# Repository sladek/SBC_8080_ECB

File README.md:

## SBC 8080 ECB microcomputer

This is my attempt to build a single-board microcomputer based on the Intel 8080 CPU. It contains the following features:

- Extended 512k x 8-bit SRAM that can be fully accessed via paging.

- 128 x 8-bit FLASH EPROM that is accessible after RESET so it can contain a bootloader, which can be moved to SRAM and boot the operating system or monitor program.

- Programmable Interrupt Controller Intel 8259.

- Programmable Interval Timer Intel 8253, which is used for baud rate generation and can also generate an interrupt and be connected to the speaker.

- Universal Synchronous/Asynchronous Receiver/Transmitter (USART) Intel 8251 used as serial console so SBC can be accessed directly via RS232 interface.

- ECB bus interface, which can be used for microcomputer extensions. The ECB bus interface facilitates communication between the main processor and various peripheral devices, enabling system expansion and enhancing functionality. Additionally, it allows for the integration of specialized hardware components, which can further optimize performance and adaptability in various applications. History of ECB bus is described below.

- Voltage power supply for CPU: +5V, -5V, +12V which follows the requirement that -5V must be the first voltage present. It also contains inverter for -5V generation and a boost converter from 5V to 12V so the SBC can be powered only from one +5V power supply.

Here you can find a schematics for the SBC. Kicad files are also available in this repository. 
[SBC_8080_ECB schematics.](Documentation/SBC_8080_ECB_.pdf)

## ECB bus history

(https://www.retrobrewcomputers.org/doku.php?id=boards:ecb:start)

Below is an image depicting the latest definition of the ECB bus as utilized by the RetroBrew Computers group. It also addresses issues related to the /RESET and /RESOUT pin definitions and the solutions implemented. This design incorporates a 3-pin jumper header to allow for the selection of the appropriate configuration.

The German firm Kontron defined what is believed to be the earliest bus using the 96-pin DIN 41612 EuroCard connectors. The bus for their Z80 offering used only the A-row and C-row pins; the B-row was left entirely unused to allow for the use of 64-pin connectors in the 96-pin format.

The earliest known RetroBrew bus definition included B-row pin definitions to facilitate the anticipated expansion of the Z80 bus to other processors, particularly Intel. To this day, the ECB SBC v2 (Z80) does not use the B-row pins.

One error occurred in defining the first RetroBrew bus: confusion between signals RESET (C-31) and RESOUT (C-26). The error resulted in a bad guess at what Kontron's intentions were with these two signals. SBC v1 (Z80) used RESET as an output from the CPU board to peripheral boards and did not use the RESOUT signal at all. Peripheral boards were designed with this assumption. When it was pointed out several years ago (I am unsure of the date) that Kontron's intention was for RESET to be an input to the CPU board only and that the CPU board would then put out a signal, RESOUT, to all of the peripheral boards in the system.

The resolution to the above mistake is that all the newer CPU and peripheral boards have a reset selection jumper to select which RetroBrew reset convention is to be used. Look for a 3-pin jumper header: shorting pins 1-2 indicates the older, erroneous, reset convention for use with older boards; shorting pins 2-3 indicates the use of the Kontron convention. The Kontron convention is essential if RESET is to be received from any of the ECB backplanes, and only newer boards are allowed in such a system. Old CPU boards have a 2-pin Reset (in) connection as well as a reset switch right on the CPU card.

## Generate baud rate for 8251

### Response:

The **8253 Programmable Interval Timer (PIT)** can be used as a **baud rate generator** for serial communication by generating clock pulses at the required frequency. This is done by programming one of its three counters to divide an input clock signal down to the desired baud rate.

### Steps to Use 8253 as Baud Rate Generator

1. **Select the Counter:** 
   The 8253 has three counters (Counter 0, Counter 1, Counter 2). You need to choose one for generating the baud rate.

2. **Provide the Clock Input:**
   
   The 8253 typically receives a clock input (e.g., **1.8432 MHz or some
   other standard clock frequency**). Ensure the clock is stable and properly connected.

3. **Calculate the Divider Value:**  
   The baud rate is generated by dividing the input clock using a counter. The formula is:
   
    Input Frequency RateDivider=Baud RateClock Input Frequency​
   
   For example, if the input clock is **1.8432 MHz** and you need a baud rate of **9600**,
   the divider value is:
   
   1843200÷9600=192

4. **Program the 8253:**
   
   - Load the
     appropriate **mode** (typically Mode 2 – Rate Generator or Mode 3 – Square Wave).
   
   - Load the **divider value** into the selected counter.
   
   - Start the timer and route its output to the serial communication hardware (like 8251 USART or UART).

5. **Connect Output to Serial**
   Device: The output of the **8253 counter** is connected to the baud rate clock input of a serial communication device like the **8251 USART** or a UART module.

### Example: Setting Baud rate for 9600 using 1.8432 MHz Clock

- Use **Counter 0** of **8253**.

- Program it in **Mode 2 (Rate Generator)**.

- Load **192** as the divider value.

#### **Programming Steps (for an x86-based system)**

Assembly code

```
    MOV AL, 34H    ; Control Word: Counter 0, Mode 2, LSB/MSB
    OUT 43H, AL    ; Send control word to 8253
    MOV AL, 192    ; Load LSB (Least Significant Byte)
    OUT 40H, AL    ; Send LSB to Counter 0
    MOV AL, 0      ; Load MSB (Most Significant Byte)
    OUT 40H, AL    ; Send MSB to Counter 0
```

- **43H** → Control port of **8253**

- **40H** → Counter 0 data port

### **Modes Used in 8253 for Baud Rate**

- **Mode 2 (Rate Generator)** → Outputs a
   frequency suitable for baud generation.

- **Mode 3 (Square Wave Generator)** → Outputs a symmetrical square wave (useful in some applications).

### **Final Connection**

The **OUT0** pin of **8253** (if using Counter 0) is connected to the **clock input** of **8251 USART or UART** for serial communication.

### **Summary**

- Use **Mode 2 (Rate Generator)**

- Compute the **divider value** using the formula

- Program the **control word and counter value**

- Connect **output** to the **serial device** clock input.

This setup allows the **8253** to act as a **baud rate generator** for serial communication.

## Baud rate divider

As crystal frequency is 18.432 Mhz and it is outputted from I8224, we can use that frequency to generate baud rate clock signal for I8251. Below is the solution.

74LS390 contains two decade counters, where /CP0 → Q0 functions as a divider by 2, and /CP1 → Q1, Q2, Q3 operates as a divider by 5. We send an 18.432 MHz clock signal from I8224 to /CP1; it is divided by 5 and then fed to /CP0, where it is divided by 2. This arrangement will generate a square signal with an exact 50% duty cycle. The output signal from Q0 is then fed to the I8252 timer, where the appropriate baud rate can be generated.

### Shadow FLASH select logic

In the picture below you can see shadow FLASH select logic schematics.

After /RESET (at this point, the /SRAMSELECT signal from the IO decoder is HIGH), /SRAM_SEL is HIGH and /FLASH_SEL is LOW. Now /SRAM_OE is HIGH (the DATA from RAM are in high impedance, although writing is not prohibited), so the /RD signal has no effect on /SRAM_OE. Only changes in /MEMRQ will impact the /FLASH_MREQ signal, which means that only FLASH memory can be accessed, either for reading or for writing. So it is also possible to flash the memory using a programmer connected to the ECB bus. A simulation has also been conducted in Verilog (via iVerilog) and can be seen below.

```
/*
 Test bench
*/

`timescale 10ns/10ns

module shadow_flash_select_logic_tb();

   reg MEMRQ, RESET, SRAMSEL, RD;
   wire SRAM_SEL, FLASH_SEL, SRAM_OE, FLASH_MEMRQ;

   initial begin
      $dumpfile ("shadow_flash_select_logic.vcd");
      $dumpvars;
   end

  initial begin
     RESET = 1;
     #10
     RESET = 0;
     #5
     RESET = 1;
  end

  initial begin
     SRAMSEL = 1;
     RD = 1;
     MEMRQ = 1;
  end

  initial begin
     #50;
       RD = 0;
     #50;
       RD = 1;
     #50;
       MEMRQ = 0;
     #50;
       MEMRQ = 1;
     #50
       SRAMSEL = 0;
     #50
       RD = 0;
     #50
       RD = 1;
     #50
       MEMRQ = 0;
     #50
       MEMRQ = 1;
 end

  initial begin
    #500;
    $finish;
  end

   // The Netlist
   nand(SRAM_SEL, RESET, FLASH_SEL);
   nand(FLASH_SEL, SRAMSEL, SRAM_SEL);
   or(SRAM_OE, SRAM_SEL, RD);
   or(FLASH_MREQ, FLASH_SEL, MEMRQ); 

endmodule
```

Simulation result in gtkwave is shown below.

### ECB bus data direction

As we also have to send and read data from the ECB bus, we have to make sure that bus data buffers are properly directed if there is a bus request (BUSRQ) from the bus itself.

Signal DATA_DIR Select the direction of the data buffer. If DATA_DIR is log 0, data direction is from the board to the ECB bus, and if DATA_DIR is log 1, 1data can flow from the ECB bus to the board.

This is done by the circuit below. Basically, the upper part (/MEMRQ, /RD, /IOSEL, which is low when internal peripherals are selected) takes care of standard operations, and the upper part is involved when there is a request from the ECB bus. (/RD, /BUSAK)

Below you can see simulation code and simulation result.

```
/*
 Test bench
*/

`timescale 10ns/10ns

module shadow_flash_select_logic_tb();

   reg MREQ, IOSEL, RD, BUSAK;
   wire DATA_DIR, MREQ_IOSEL, RD_BUSAK, DATAEN;

   initial begin
      $dumpfile ("ecb_data_dir_logic.vcd");
      $dumpvars;
   end

  initial begin
    MREQ = 1;
    IOSEL = 1;
    RD = 1;
    BUSAK = 1;
/* MREQ and RD */
    #50
      MREQ = 0;
    #10
      RD = 0;
    #50
      RD = 1;
    #10
      MREQ = 1;
/* IOSEL and RD */
    #50
      IOSEL = 0;
    #10
      RD = 0;
    #50
      RD = 1;
    #10
      IOSEL = 1;
/* BUSAK and RD */
    #50
      BUSAK = 0;
    #50
      BUSAK = 1;
    #50
      RD = 0;
    #50
      RD = 1;
  end

  initial begin
    #500;
    $finish;
  end

   // The Netlist
   and(MREQ_IOSEL, MREQ, IOSEL);
   nand(RD_BUSAK, RD, BUSAK);
   or(RD_MREQ_IOSEL, MREQ_IOSEL, RD);
   and(DATA_DIR, RD_MREQ_IOSEL, RD_BUSAK);

endmodule
```

And the simulation result is below.

### Peripherals address space

Internal peripherals are selected by the following decoder.

The address space with this circuit is 0x40 – 0x7f.

Where base addresses of peripherals are in the following table.

|                                                   |               |
| ------------------------------------------------- | ------------- |
| Peripheral                                        | Address range |
| PIC 8259A                                         | 0x40 – 047    |
| PIT 8253                                          | 0x48 - 0x4F   |
| SIO 8251                                          | 0x50 - 0x57   |
| RAM bank/ SD card select register (/BANK/SD_SEL ) | 0x58 - 0x5F   |
| RAM select signal (/SRAMSEL)                      | 0x78 - 0x7F   |

Below is verilog simulation result for the decoder.

And the source code. I intentionally use primitives for simulation of 74LS138 to prevent some simulation glitches I got when I tried to use behavioral modeling. It is quite simplified as I’ve just wanted to verify address space for peripherals.

```
/*
 Test bench
*/

`timescale 10ns/10ns

module SN74LS138(input [2:0] ADDR, input E0_n, E1_n, E2, output wire [7:0] Y_n);

  not(E2_n, E2);
  nor(ENBL, E2_n, E0_n, E1_n);
  not(A_n, ADDR[0]);
  not(B_n, ADDR[1]);
  not(C_n, ADDR[2]);
  not(A, A_n);
  not(B, B_n);
  not(C, C_n);
  nand(Y_n[0], A_n, B_n, C_n, ENBL);
  nand(Y_n[1], A, B_n, C_n, ENBL);
  nand(Y_n[2], A_n, B, C_n, ENBL);
  nand(Y_n[3], A, B, C_n, ENBL);
  nand(Y_n[4], A_n, B_n, C, ENBL);
  nand(Y_n[5], A, B_n, C, ENBL);
  nand(Y_n[6], A_n, B, C, ENBL);
  nand(Y_n[7], A, B, C, ENBL);

endmodule

module peripheral_decoder_tb();
  reg  [7:0] ADDRESS = 0;
  reg  A6, A7, IORQ_n;
  wire [7:0] OUT;
  wire A7_n, A7_A6, IOSEL_n, PIC_SEL_n, PIT_SEL_n, SIO_SEL_n, SD_SEL_n, BANK_SD_SEL_n;
  integer I = 0;

   initial begin
      $dumpfile ("peripheral_decoder.vcd");
      $dumpvars;
   end

  initial begin
    IORQ_n = 0;
    ADDRESS = 'h00;
    for ( I = 'h3F ; I < 'hff; I = I + 1) begin
      #5 ADDRESS = I;
    end

  end

  initial begin
    #350;
    $finish;
  end
  assign PIC_SEL_n = OUT[0];
  assign PIT_SEL_n = OUT[1];
  assign SIO_SEL_n = OUT[2];
  assign SD_SEL_n = OUT[3];
  assign BANK_SD_SEL_n = OUT[7];
  // The Netlist
  SN74LS138 ls138(ADDRESS[5:3], IOSEL_n, IOSEL_n, 1'b1 , OUT);
  not(A7_n, ADDRESS[7]);
  nand(A7_A6, A7_n, ADDRESS[6]);
  or(IOSEL_n, A7_A6, IORQ_n);
endmodule
```

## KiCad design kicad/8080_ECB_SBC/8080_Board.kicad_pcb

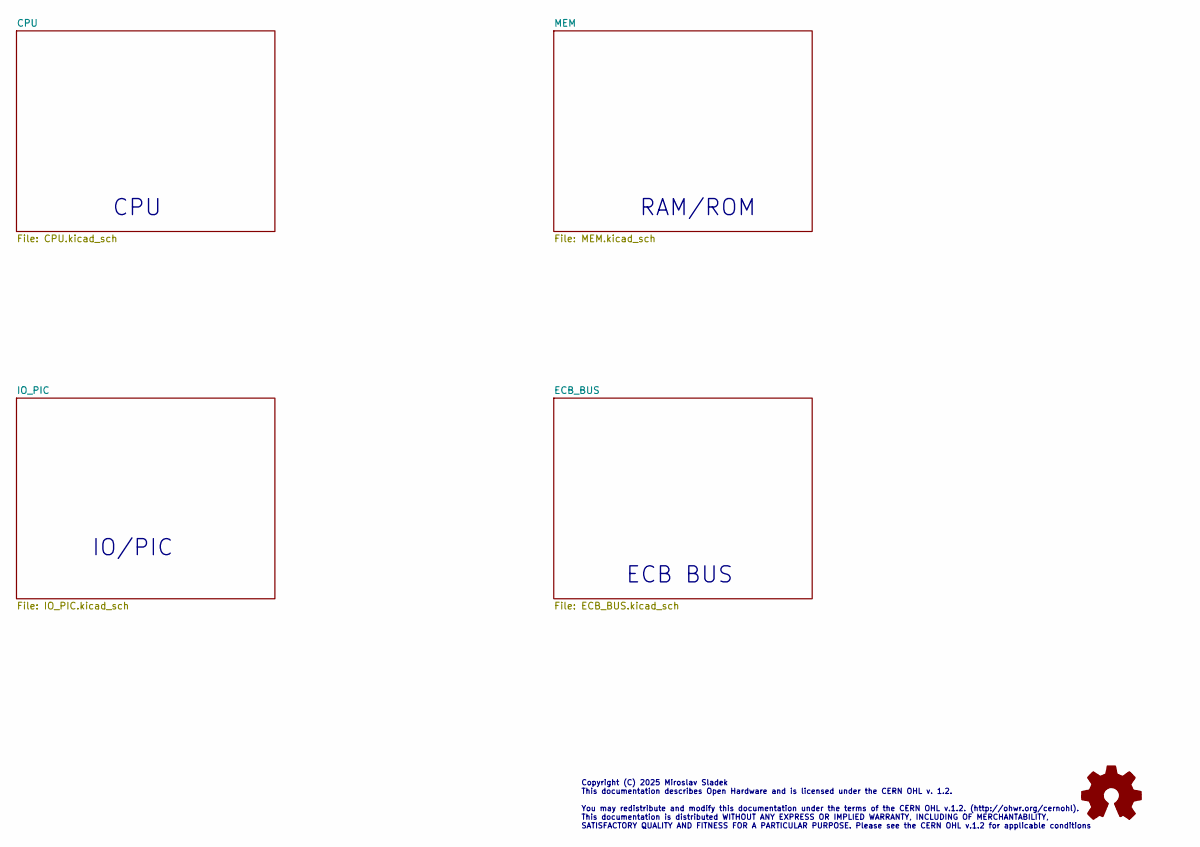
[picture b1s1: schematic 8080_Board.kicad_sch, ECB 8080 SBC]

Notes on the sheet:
RAM/ROM
IO/PIC
CPU
ECB BUS
Copyright (C) 2025 Miroslav Sladek This documentation describes Open Hardware and is licensed under the CERN OHL v. 1.2. You may redistribute and modify this documentation under the terms of the CERN OHL v.1.2. (http://ohwr.org/cernohl). This documentation is distributed WITHOUT ANY EXPRESS OR IMPL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

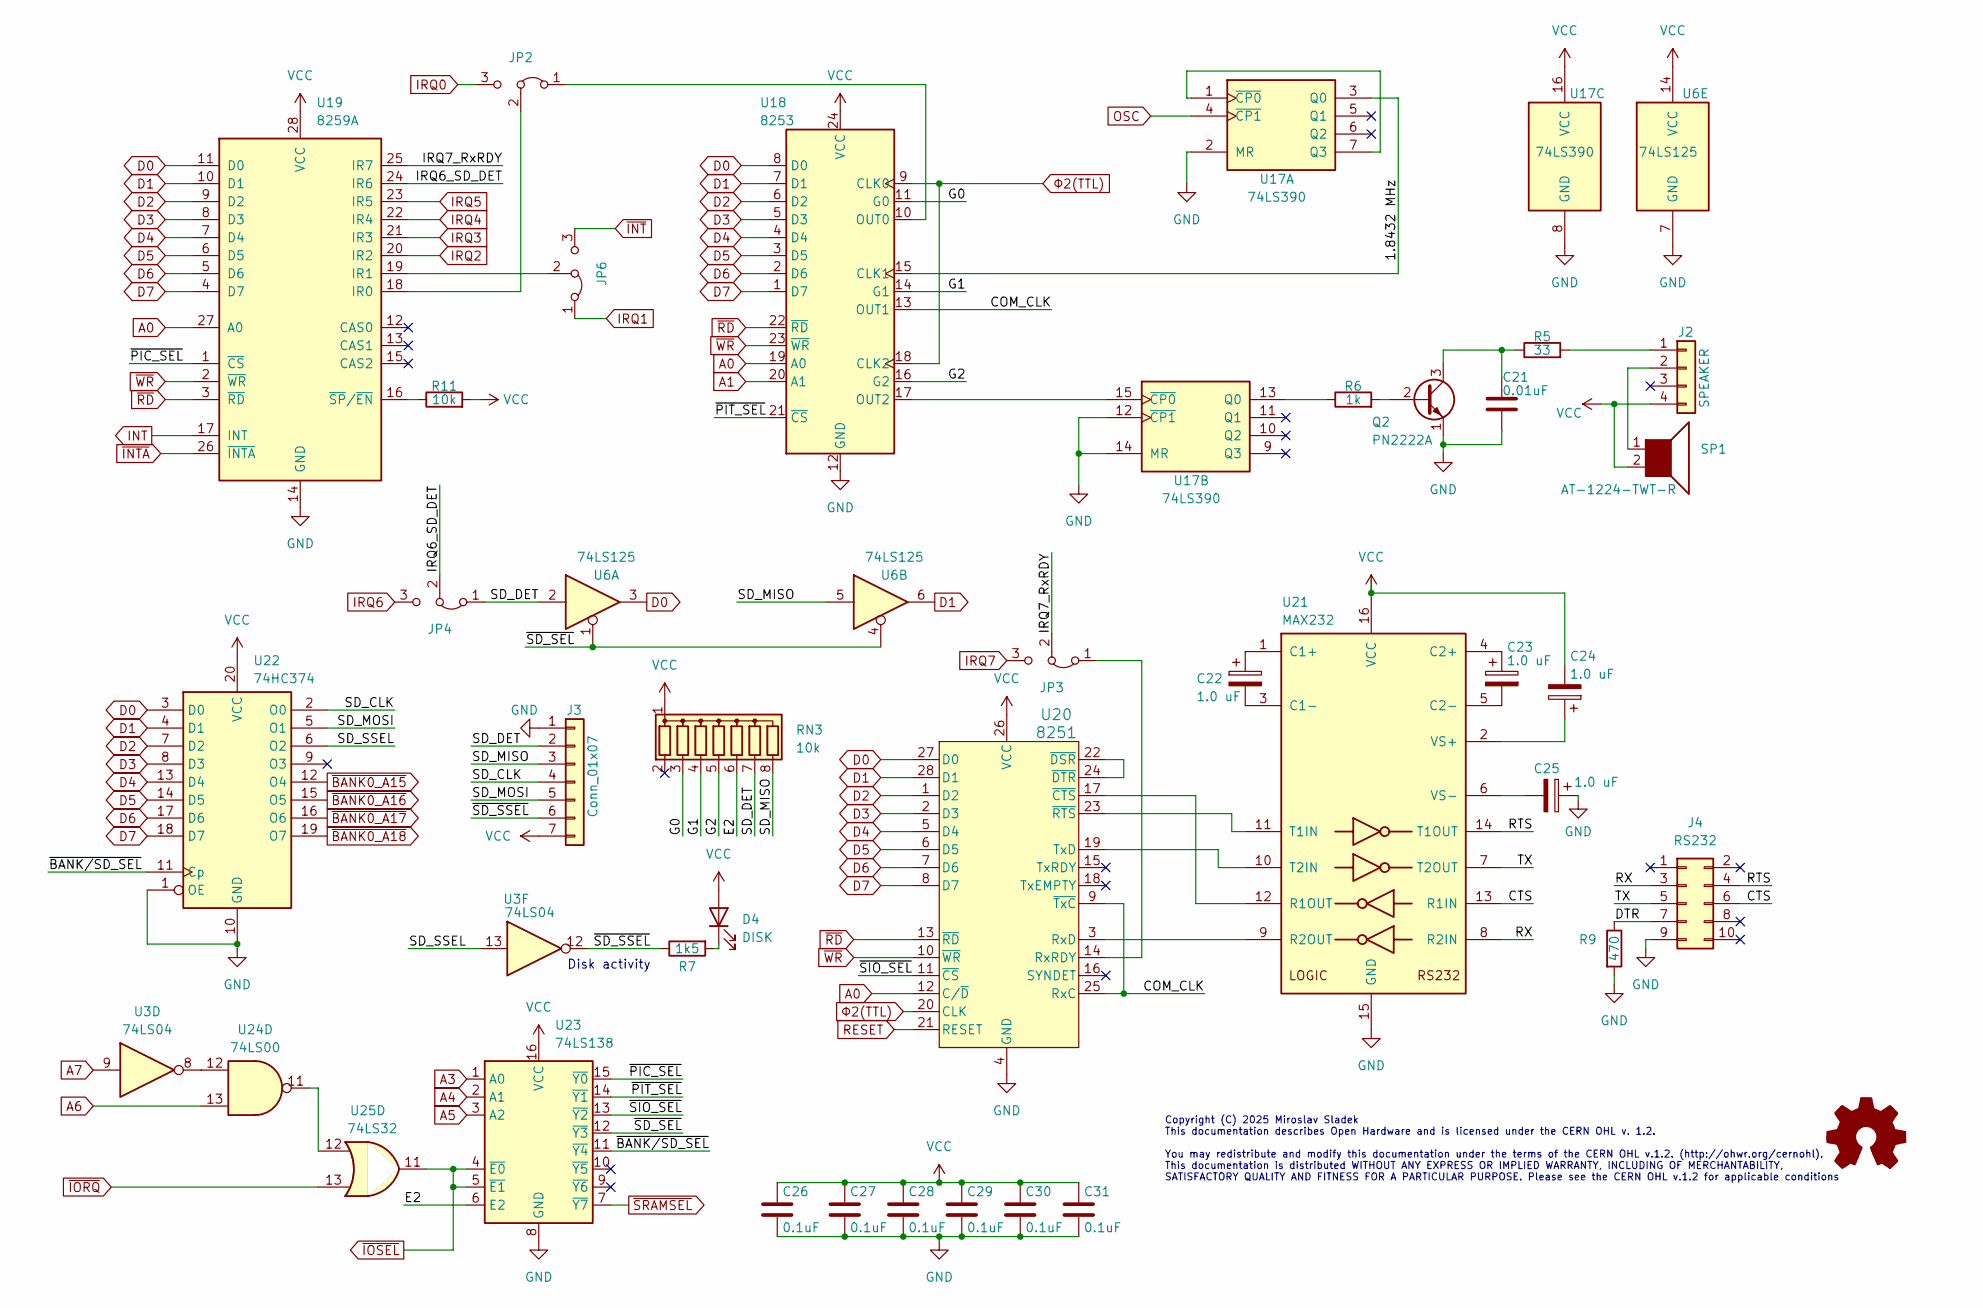
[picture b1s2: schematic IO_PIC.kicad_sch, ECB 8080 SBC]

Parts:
C21: 0.01uF; C_Disc_D3.0mm_W1.6mm_P2.50mm
C22, C23, C24, C25: 1.0 uF; C_Rect_L7.2mm_W3.0mm_P5.00mm_FKS2_FKP2_MKS2_MKP2
C26, C27, C28, C29, C30, C31: 0.1uF; C_Disc_D4.3mm_W1.9mm_P5.00mm
D4: DISK; LED_D3.0mm
J2: SPEAKER; PinHeader_1x04_P2.54mm_Vertical
J3: Conn_01x07; PinSocket_1x07_P2.54mm_Vertical
J4: RS232; PinHeader_2x05_P2.54mm_Vertical
JP2, JP3, JP4, JP6: Jumper_3_Bridged12; PinHeader_1x03_P2.54mm_Vertical
Q2: PN2222A; TO-92_Inline
R5: 33; R_Axial_DIN0204_L3.6mm_D1.6mm_P7.62mm_Horizontal
R6: 1k; R_Axial_DIN0204_L3.6mm_D1.6mm_P7.62mm_Horizontal
R7: 1k5; R_Axial_DIN0204_L3.6mm_D1.6mm_P7.62mm_Horizontal
R9: 470; R_Axial_DIN0204_L3.6mm_D1.6mm_P7.62mm_Horizontal
R11: 10k; R_Axial_DIN0204_L3.6mm_D1.6mm_P7.62mm_Horizontal
RN3: 10k; R_Array_SIP8
SP1: AT-1224-TWT-R; MagneticBuzzer_ProSignal_ABT-410-RC
U3: 74LS04; DIP-14_W7.62mm_Socket
U6: 74LS125; DIP-14_W7.62mm_Socket
U17: 74LS390; DIP-16_W7.62mm_Socket
U18: 8253; DIP-24_W15.24mm_Socket
U19: 8259A; DIP-28_W15.24mm_Socket
U20: 8251; DIP-28_W15.24mm_Socket
U21: MAX232; DIP-16_W7.62mm_Socket
U22: 74HC374; DIP-20_W7.62mm_Socket
U23: 74LS138; DIP-16_W7.62mm_Socket
U24: 74LS00; DIP-14_W7.62mm_Socket
U25: 74LS32; DIP-14_W7.62mm_Socket

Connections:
/IO_PIC/1.8432 MHz: U17.3 (Q0), U18.15 (CLK1)
/IO_PIC/COM_CLK: U18.13 (OUT1), U20.9 (~TxC), U20.25 (RxC)
/IO_PIC/CTS: J4.6, U21.13 (R1IN)
/IO_PIC/DTR: J4.7, R9.1
/IO_PIC/E2: RN3.6 (R5), U23.6 (E2)
/IO_PIC/G0: RN3.3 (R2), U18.11 (G0)
/IO_PIC/G1: RN3.4 (R3), U18.14 (G1)
/IO_PIC/G2: RN3.5 (R4), U18.16 (G2)
/IO_PIC/IRQ6_SD_DET: JP4.2 (C), U19.24 (IR6)
/IO_PIC/IRQ7_RxRDY: JP3.2 (C), U19.25 (IR7)
/IO_PIC/RTS: J4.4, U21.14 (T1OUT)
/IO_PIC/RX: J4.3, U21.8 (R2IN)
/IO_PIC/SD_CLK: J3.4, U22.2 (O0)
/IO_PIC/SD_DET: J3.2, JP4.1 (A), RN3.7 (R6), U6.2
/IO_PIC/SD_MISO: J3.3, RN3.8 (R7), U6.5
/IO_PIC/SD_MOSI: J3.5, U22.5 (O1)
/IO_PIC/SD_SSEL: U3.13, U22.6 (O2)
/IO_PIC/TX: J4.5, U21.7 (T2OUT)
/IO_PIC/~BANK/SD_SEL: U22.11 (Cp), U23.11 (~Y4)
/IO_PIC/~PIC_SEL: U19.1 (~CS), U23.15 (~Y0)
/IO_PIC/~PIT_SEL: U18.21 (~CS), U23.14 (~Y1)
/IO_PIC/~SD_SEL: U6.1, U6.4, U23.12 (~Y3)
/IO_PIC/~SD_SSEL: J3.6, R7.1, U3.12
/IO_PIC/~SIO_SEL: U20.11 (~CS), U23.13 (~Y2)
A0: U18.19 (A0), U19.27 (A0), U20.12 (C/~D); also elsewhere on the board
A1: U18.20 (A1); also elsewhere on the board
A3: U23.1 (A0); also elsewhere on the board
A4: U23.2 (A1); also elsewhere on the board
A5: U23.3 (A2); also elsewhere on the board
A6: U24.13; also elsewhere on the board
A7: U3.9; also elsewhere on the board
D0: U6.3, U18.8 (D0), U19.11 (D0), U20.27 (D0), U22.3 (D0); also elsewhere on the board
D1: U6.6, U18.7 (D1), U19.10 (D1), U20.28 (D1), U22.4 (D1); also elsewhere on the board
D2: U18.6 (D2), U19.9 (D2), U20.1 (D2), U22.7 (D2); also elsewhere on the board
D3: U18.5 (D3), U19.8 (D3), U20.2 (D3), U22.8 (D3); also elsewhere on the board
D4: U18.4 (D4), U19.7 (D4), U20.5 (D4), U22.13 (D4); also elsewhere on the board
D5: U18.3 (D5), U19.6 (D5), U20.6 (D5), U22.14 (D5); also elsewhere on the board
D6: U18.2 (D6), U19.5 (D6), U20.7 (D6), U22.17 (D6); also elsewhere on the board
D7: U18.1 (D7), U19.4 (D7), U20.8 (D7), U22.18 (D7); also elsewhere on the board
INT: U19.17 (INT); also elsewhere on the board
IRQ0: JP2.3 (B); also elsewhere on the board
IRQ1: JP6.1 (A); also elsewhere on the board
IRQ2: U19.20 (IR2); also elsewhere on the board
IRQ3: U19.21 (IR3); also elsewhere on the board
IRQ4: U19.22 (IR4); also elsewhere on the board
IRQ5: U19.23 (IR5); also elsewhere on the board
IRQ6: JP4.3 (B); also elsewhere on the board
IRQ7: JP3.3 (B); also elsewhere on the board
unnamed: D4.1 (K), R7.2
unnamed: J2.1, R5.2
unnamed: J2.2, SP1.1
unnamed: JP2.1 (A), U18.10 (OUT0)
unnamed: JP2.2 (C), U19.18 (IR0)
unnamed: JP3.1 (A), U20.14 (RxRDY)
unnamed: JP6.2 (C), U19.19 (IR1)
unnamed: Q2.2 (B), R6.2
unnamed: C21.1, Q2.3 (C), R5.1
unnamed: U17.1 (~CP0), U17.7 (Q3)
unnamed: R6.1, U17.13 (Q0)
unnamed: U17.15 (~CP0), U18.17 (OUT2)
unnamed: R11.1, U19.16 (~SP/~EN)
unnamed: U20.3 (RxD), U21.9 (R2OUT)
unnamed: U20.19 (TxD), U21.10 (T2IN)
unnamed: U20.17 (~CTS), U21.12 (R1OUT)
unnamed: U20.22 (~DSR), U20.24 (~DTR)
unnamed: U20.23 (~RTS), U21.11 (T1IN)
unnamed: C22.1, U21.1 (C1+)
unnamed: C22.2, U21.3 (C1-)
unnamed: C23.1, U21.4 (C2+)
unnamed: C23.2, U21.5 (C2-)
unnamed: C24.1, U21.2 (VS+)
unnamed: C25.2, U21.6 (VS-)
unnamed: U24.11, U25.12
unnamed: U3.8, U24.12
OSC: U17.4 (~CP1); also elsewhere on the board
RESET: U20.21 (RESET); also elsewhere on the board
VCC: C24.2, C26.1, C27.1, C28.1, C29.1, C30.1, C31.1, D4.2 (A), J2.4, J3.7, R11.2, RN3.1 (common), SP1.2, U6.14 (VCC), U17.16 (VCC), U18.24 (VCC), U19.28 (VCC), U20.26 (VCC), U21.16 (VCC), U22.20 (VCC), U23.16 (VCC); also elsewhere on the board
~BANK0_A15: U22.12 (O4); also elsewhere on the board
~BANK0_A16: U22.15 (O5); also elsewhere on the board
~BANK0_A17: U22.16 (O6); also elsewhere on the board
~BANK0_A18: U22.19 (O7); also elsewhere on the board
~INTA: U19.26 (~INTA); also elsewhere on the board
~INT: JP6.3 (B); also elsewhere on the board
~IORQ: U25.13; also elsewhere on the board
~IOSEL: U23.4 (~E0), U23.5 (~E1), U25.11; also elsewhere on the board
~RD: U18.22 (~RD), U19.3 (~RD), U20.13 (~RD); also elsewhere on the board
~SRAMSEL: U23.7 (~Y7); also elsewhere on the board
~WR: U18.23 (~WR), U19.2 (~WR), U20.10 (~WR); also elsewhere on the board
Φ2(TTL): U18.9 (CLK0), U18.18 (CLK2), U20.20 (CLK); also elsewhere on the board

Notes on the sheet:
Disk activity
Copyright (C) 2025 Miroslav Sladek This documentation describes Open Hardware and is licensed under the CERN OHL v. 1.2. You may redistribute and modify this documentation under the terms of the CERN OHL v.1.2. (http://ohwr.org/cernohl). This documentation is distributed WITHOUT ANY EXPRESS OR IMPL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

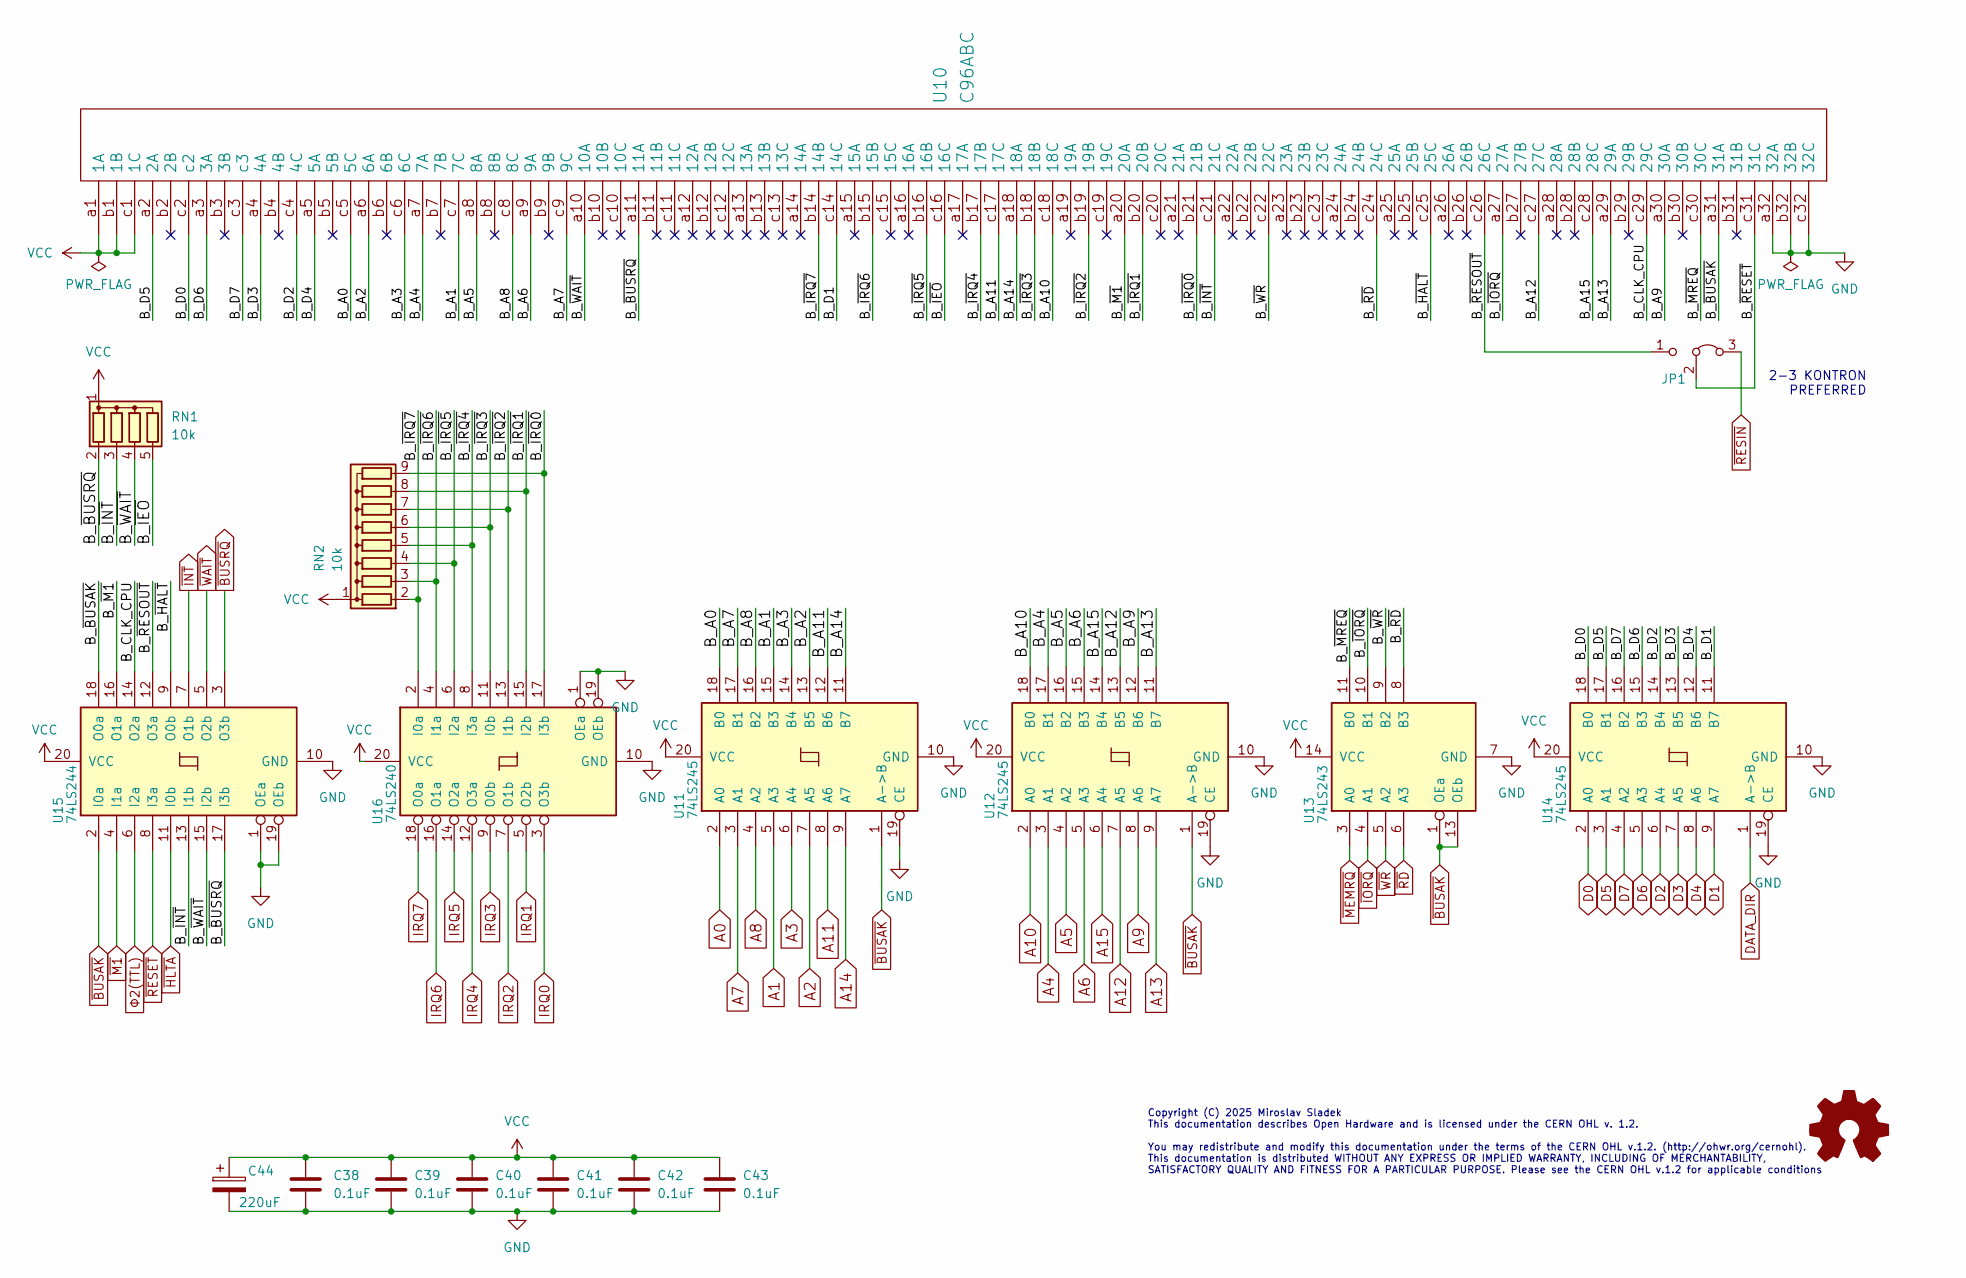
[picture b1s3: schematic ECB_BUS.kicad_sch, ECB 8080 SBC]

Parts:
C38, C39, C40, C41, C42, C43: 0.1uF; C_Disc_D4.3mm_W1.9mm_P5.00mm
C44: 220uF; CP_Radial_D5.0mm_P2.00mm
JP1: Jumper_3_Bridged23; PinHeader_1x03_P2.54mm_Vertical
RN1: 10k; R_Array_SIP5
RN2: 10k; R_Array_SIP9
U10: C96ABC; DIN41612_C_3x32_Male_Horizontal_THT
U11, U12, U14: 74LS245; DIP-20_W7.62mm_Socket
U13: 74LS243; DIP-14_W7.62mm_Socket
U15: 74LS244; DIP-20_W7.62mm_Socket
U16: 74LS240; DIP-20_W7.62mm_Socket

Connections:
/ECB_BUS/B_A0: U10.c5 (5C), U11.18 (B0)
/ECB_BUS/B_A1: U10.c7 (7C), U11.15 (B3)
/ECB_BUS/B_A2: U10.a6 (6A), U11.13 (B5)
/ECB_BUS/B_A3: U10.c6 (6C), U11.14 (B4)
/ECB_BUS/B_A4: U10.a7 (7A), U12.17 (B1)
/ECB_BUS/B_A5: U10.a8 (8A), U12.16 (B2)
/ECB_BUS/B_A6: U10.a9 (9A), U12.15 (B3)
/ECB_BUS/B_A7: U10.c9 (9C), U11.17 (B1)
/ECB_BUS/B_A8: U10.c8 (8C), U11.16 (B2)
/ECB_BUS/B_A9: U10.a30 (30A), U12.12 (B6)
/ECB_BUS/B_A10: U10.c18 (18C), U12.18 (B0)
/ECB_BUS/B_A11: U10.c17 (17C), U11.12 (B6)
/ECB_BUS/B_A12: U10.c27 (27C), U12.13 (B5)
/ECB_BUS/B_A13: U10.a29 (29A), U12.11 (B7)
/ECB_BUS/B_A14: U10.a18 (18A), U11.11 (B7)
/ECB_BUS/B_A15: U10.c28 (28C), U12.14 (B4)
/ECB_BUS/B_CLK_CPU: U10.c29 (29C), U15.14 (O2a)
/ECB_BUS/B_D0: U10.c2, U14.18 (B0)
/ECB_BUS/B_D1: U10.c14 (14C), U14.11 (B7)
/ECB_BUS/B_D2: U10.c4 (4C), U14.14 (B4)
/ECB_BUS/B_D3: U10.a4 (4A), U14.13 (B5)
/ECB_BUS/B_D4: U10.a5 (5A), U14.12 (B6)
/ECB_BUS/B_D5: U10.a2 (2A), U14.17 (B1)
/ECB_BUS/B_D6: U10.a3 (3A), U14.15 (B3)
/ECB_BUS/B_D7: U10.c3, U14.16 (B2)
/ECB_BUS/B_~BUSAK: U10.a31 (31A), U15.18 (O0a)
/ECB_BUS/B_~BUSRQ: RN1.2 (R1), U10.a11 (11A), U15.17 (I3b)
/ECB_BUS/B_~HALT: U10.c25 (25C), U15.9 (O0b)
/ECB_BUS/B_~IEO: RN1.5 (R4), U10.c16 (16C)
/ECB_BUS/B_~INT: RN1.3 (R2), U10.c21 (21C), U15.13 (I1b)
/ECB_BUS/B_~IORQ: U10.a27 (27A), U13.10 (B1)
/ECB_BUS/B_~IRQ0: RN2.9 (R8), U10.b21 (21B), U16.17 (I3b)
/ECB_BUS/B_~IRQ1: RN2.8 (R7), U10.b20 (20B), U16.15 (I2b)
/ECB_BUS/B_~IRQ2: RN2.7 (R6), U10.b19 (19B), U16.13 (I1b)
/ECB_BUS/B_~IRQ3: RN2.6 (R5), U10.b18 (18B), U16.11 (I0b)
/ECB_BUS/B_~IRQ4: RN2.5 (R4), U10.b17 (17B), U16.8 (I3a)
/ECB_BUS/B_~IRQ5: RN2.4 (R3), U10.b16 (16B), U16.6 (I2a)
/ECB_BUS/B_~IRQ6: RN2.3 (R2), U10.b15 (15B), U16.4 (I1a)
/ECB_BUS/B_~IRQ7: RN2.2 (R1), U10.b14 (14B), U16.2 (I0a)
/ECB_BUS/B_~M1: U10.a20 (20A), U15.16 (O1a)
/ECB_BUS/B_~MREQ: U10.c30 (30C), U13.11 (B0)
/ECB_BUS/B_~RD: U10.c24 (24C), U13.8 (B3)
/ECB_BUS/B_~RESET: JP1.2 (C), U10.c31 (31C)
/ECB_BUS/B_~RESOUT: JP1.1 (A), U10.c26 (26C), U15.12 (O3a)
/ECB_BUS/B_~WAIT: RN1.4 (R3), U10.a10 (10A), U15.15 (I2b)
/ECB_BUS/B_~WR: U10.c22 (22C), U13.9 (B2)
A0: U11.2 (A0); also elsewhere on the board
A1: U11.5 (A3); also elsewhere on the board
A2: U11.7 (A5); also elsewhere on the board
A3: U11.6 (A4); also elsewhere on the board
A4: U12.3 (A1); also elsewhere on the board
A5: U12.4 (A2); also elsewhere on the board
A6: U12.5 (A3); also elsewhere on the board
A7: U11.3 (A1); also elsewhere on the board
A8: U11.4 (A2); also elsewhere on the board
A9: U12.8 (A6); also elsewhere on the board
A10: U12.2 (A0); also elsewhere on the board
A11: U11.8 (A6); also elsewhere on the board
A12: U12.7 (A5); also elsewhere on the board
A13: U12.9 (A7); also elsewhere on the board
A14: U11.9 (A7); also elsewhere on the board
A15: U12.6 (A4); also elsewhere on the board
D0: U14.2 (A0); also elsewhere on the board
D1: U14.9 (A7); also elsewhere on the board
D2: U14.6 (A4); also elsewhere on the board
D3: U14.7 (A5); also elsewhere on the board
D4: U14.8 (A6); also elsewhere on the board
D5: U14.3 (A1); also elsewhere on the board
D6: U14.5 (A3); also elsewhere on the board
D7: U14.4 (A2); also elsewhere on the board
DATA_DIR: U14.1 (A->B); also elsewhere on the board
IRQ0: U16.3 (O3b); also elsewhere on the board
IRQ1: U16.5 (O2b); also elsewhere on the board
IRQ2: U16.7 (O1b); also elsewhere on the board
IRQ3: U16.9 (O0b); also elsewhere on the board
IRQ4: U16.12 (O3a); also elsewhere on the board
IRQ5: U16.14 (O2a); also elsewhere on the board
IRQ6: U16.16 (O1a); also elsewhere on the board
IRQ7: U16.18 (O0a); also elsewhere on the board
VCC: C38.1, C39.1, C40.1, C41.1, C42.1, C43.1, C44.1, RN1.1 (common), RN2.1 (common), U10.a1 (1A), U10.b1 (1B), U10.c1 (1C), U11.20 (VCC), U12.20 (VCC), U13.14 (VCC), U14.20 (VCC), U15.20 (VCC), U16.20 (VCC); also elsewhere on the board
~BUSAK: U11.1 (A->B), U12.1 (A->B), U13.1 (OEa), U13.13 (OEb), U15.2 (I0a); also elsewhere on the board
~BUSRQ: U15.3 (O3b); also elsewhere on the board
~HLTA: U15.11 (I0b); also elsewhere on the board
~INT: U15.7 (O1b); also elsewhere on the board
~IORQ: U13.4 (A1); also elsewhere on the board
~M1: U15.4 (I1a); also elsewhere on the board
~MEMRQ: U13.3 (A0); also elsewhere on the board
~RD: U13.6 (A3); also elsewhere on the board
~RESET: U15.8 (I3a); also elsewhere on the board
~RESIN: JP1.3 (B); also elsewhere on the board
~WAIT: U15.5 (O2b); also elsewhere on the board
~WR: U13.5 (A2); also elsewhere on the board
Φ2(TTL): U15.6 (I2a); also elsewhere on the board

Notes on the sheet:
2-3 KONTRON PREFERRED
Copyright (C) 2025 Miroslav Sladek This documentation describes Open Hardware and is licensed under the CERN OHL v. 1.2. You may redistribute and modify this documentation under the terms of the CERN OHL v.1.2. (http://ohwr.org/cernohl). This documentation is distributed WITHOUT ANY EXPRESS OR IMPL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

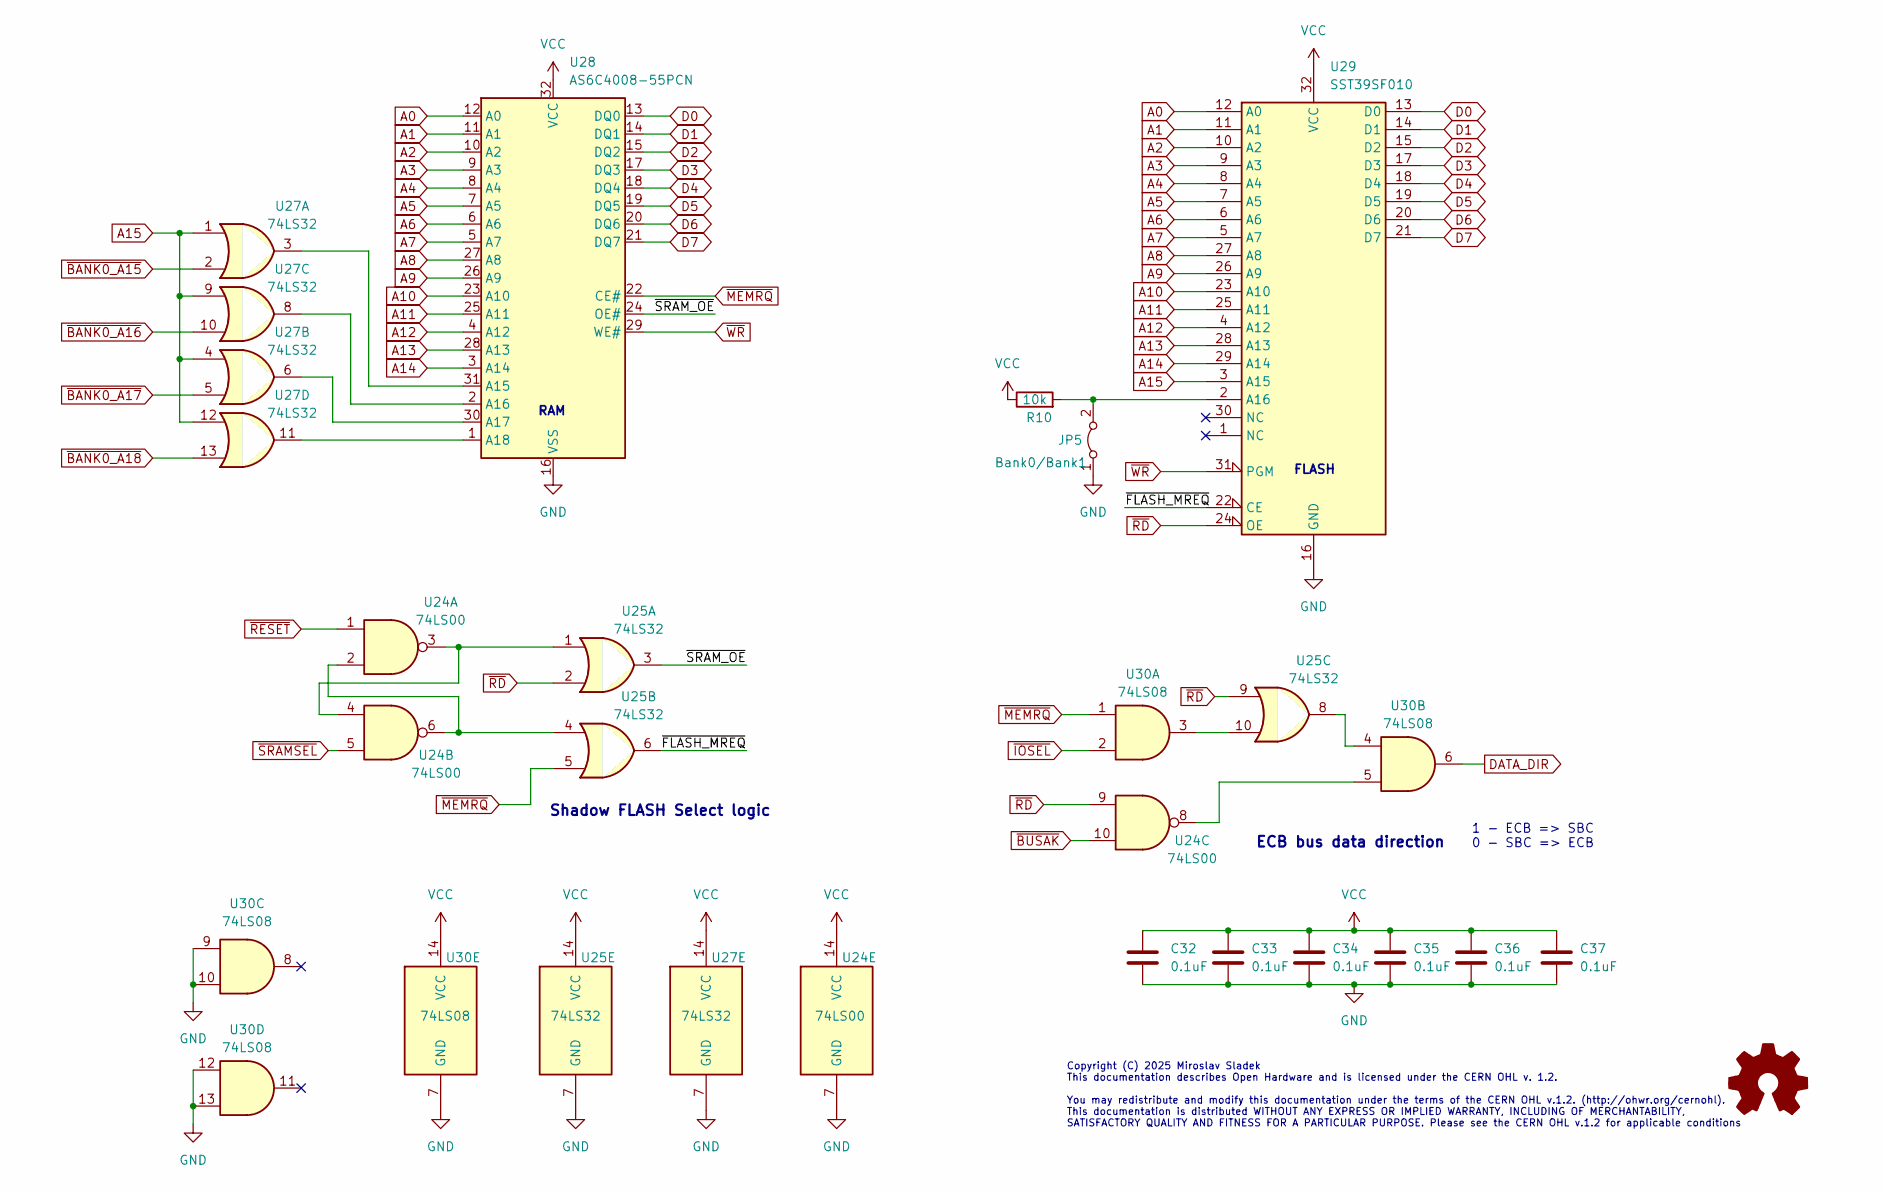
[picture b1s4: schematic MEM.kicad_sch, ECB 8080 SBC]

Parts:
C32, C33, C34, C35, C36, C37: 0.1uF; C_Disc_D4.3mm_W1.9mm_P5.00mm
JP5: Bank0/Bank1; PinHeader_1x02_P2.54mm_Vertical
R10: 10k; R_Axial_DIN0204_L3.6mm_D1.6mm_P7.62mm_Horizontal
U24: 74LS00; DIP-14_W7.62mm_Socket
U25, U27: 74LS32; DIP-14_W7.62mm_Socket
U28: AS6C4008-55PCN; DIP-32_W15.24mm_Socket
U29: SST39SF010; DIP-32_W15.24mm_Socket
U30: 74LS08; DIP-14_W7.62mm_Socket

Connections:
/MEM/~FLASH_MREQ: U25.6, U29.22 (CE)
/MEM/~SRAM_OE: U25.3, U28.24 (OE#)
A0: U28.12 (A0), U29.12 (A0); also elsewhere on the board
A1: U28.11 (A1), U29.11 (A1); also elsewhere on the board
A2: U28.10 (A2), U29.10 (A2); also elsewhere on the board
A3: U28.9 (A3), U29.9 (A3); also elsewhere on the board
A4: U28.8 (A4), U29.8 (A4); also elsewhere on the board
A5: U28.7 (A5), U29.7 (A5); also elsewhere on the board
A6: U28.6 (A6), U29.6 (A6); also elsewhere on the board
A7: U28.5 (A7), U29.5 (A7); also elsewhere on the board
A8: U28.27 (A8), U29.27 (A8); also elsewhere on the board
A9: U28.26 (A9), U29.26 (A9); also elsewhere on the board
A10: U28.23 (A10), U29.23 (A10); also elsewhere on the board
A11: U28.25 (A11), U29.25 (A11); also elsewhere on the board
A12: U28.4 (A12), U29.4 (A12); also elsewhere on the board
A13: U28.28 (A13), U29.28 (A13); also elsewhere on the board
A14: U28.3 (A14), U29.29 (A14); also elsewhere on the board
A15: U27.1, U27.4, U27.9, U27.12, U29.3 (A15); also elsewhere on the board
D0: U28.13 (DQ0), U29.13 (D0); also elsewhere on the board
D1: U28.14 (DQ1), U29.14 (D1); also elsewhere on the board
D2: U28.15 (DQ2), U29.15 (D2); also elsewhere on the board
D3: U28.17 (DQ3), U29.17 (D3); also elsewhere on the board
D4: U28.18 (DQ4), U29.18 (D4); also elsewhere on the board
D5: U28.19 (DQ5), U29.19 (D5); also elsewhere on the board
D6: U28.20 (DQ6), U29.20 (D6); also elsewhere on the board
D7: U28.21 (DQ7), U29.21 (D7); also elsewhere on the board
DATA_DIR: U30.6; also elsewhere on the board
unnamed: JP5.2 (B), R10.2, U29.2 (A16)
unnamed: U24.2, U24.6, U25.4
unnamed: U24.3, U24.4, U25.1
unnamed: U24.8, U30.5
unnamed: U25.8, U30.4
unnamed: U25.10, U30.3
unnamed: U27.3, U28.31 (A15)
unnamed: U27.8, U28.2 (A16)
unnamed: U27.6, U28.30 (A17)
unnamed: U27.11, U28.1 (A18)
VCC: C32.1, C33.1, C34.1, C35.1, C36.1, C37.1, R10.1, U24.14 (VCC), U25.14 (VCC), U27.14 (VCC), U28.32 (VCC), U29.32 (VCC), U30.14 (VCC); also elsewhere on the board
~BANK0_A15: U27.2; also elsewhere on the board
~BANK0_A16: U27.10; also elsewhere on the board
~BANK0_A17: U27.5; also elsewhere on the board
~BANK0_A18: U27.13; also elsewhere on the board
~BUSAK: U24.10; also elsewhere on the board
~IOSEL: U30.2; also elsewhere on the board
~MEMRQ: U25.5, U28.22 (CE#), U30.1; also elsewhere on the board
~RD: U24.9, U25.2, U25.9, U29.24 (OE); also elsewhere on the board
~RESET: U24.1; also elsewhere on the board
~SRAMSEL: U24.5; also elsewhere on the board
~WR: U28.29 (WE#), U29.31 (PGM); also elsewhere on the board

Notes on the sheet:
FLASH
ECB bus data direction
Shadow FLASH Select logic
1 - ECB => SBC 0 - SBC => ECB
RAM
Copyright (C) 2025 Miroslav Sladek This documentation describes Open Hardware and is licensed under the CERN OHL v. 1.2. You may redistribute and modify this documentation under the terms of the CERN OHL v.1.2. (http://ohwr.org/cernohl). This documentation is distributed WITHOUT ANY EXPRESS OR IMPL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
